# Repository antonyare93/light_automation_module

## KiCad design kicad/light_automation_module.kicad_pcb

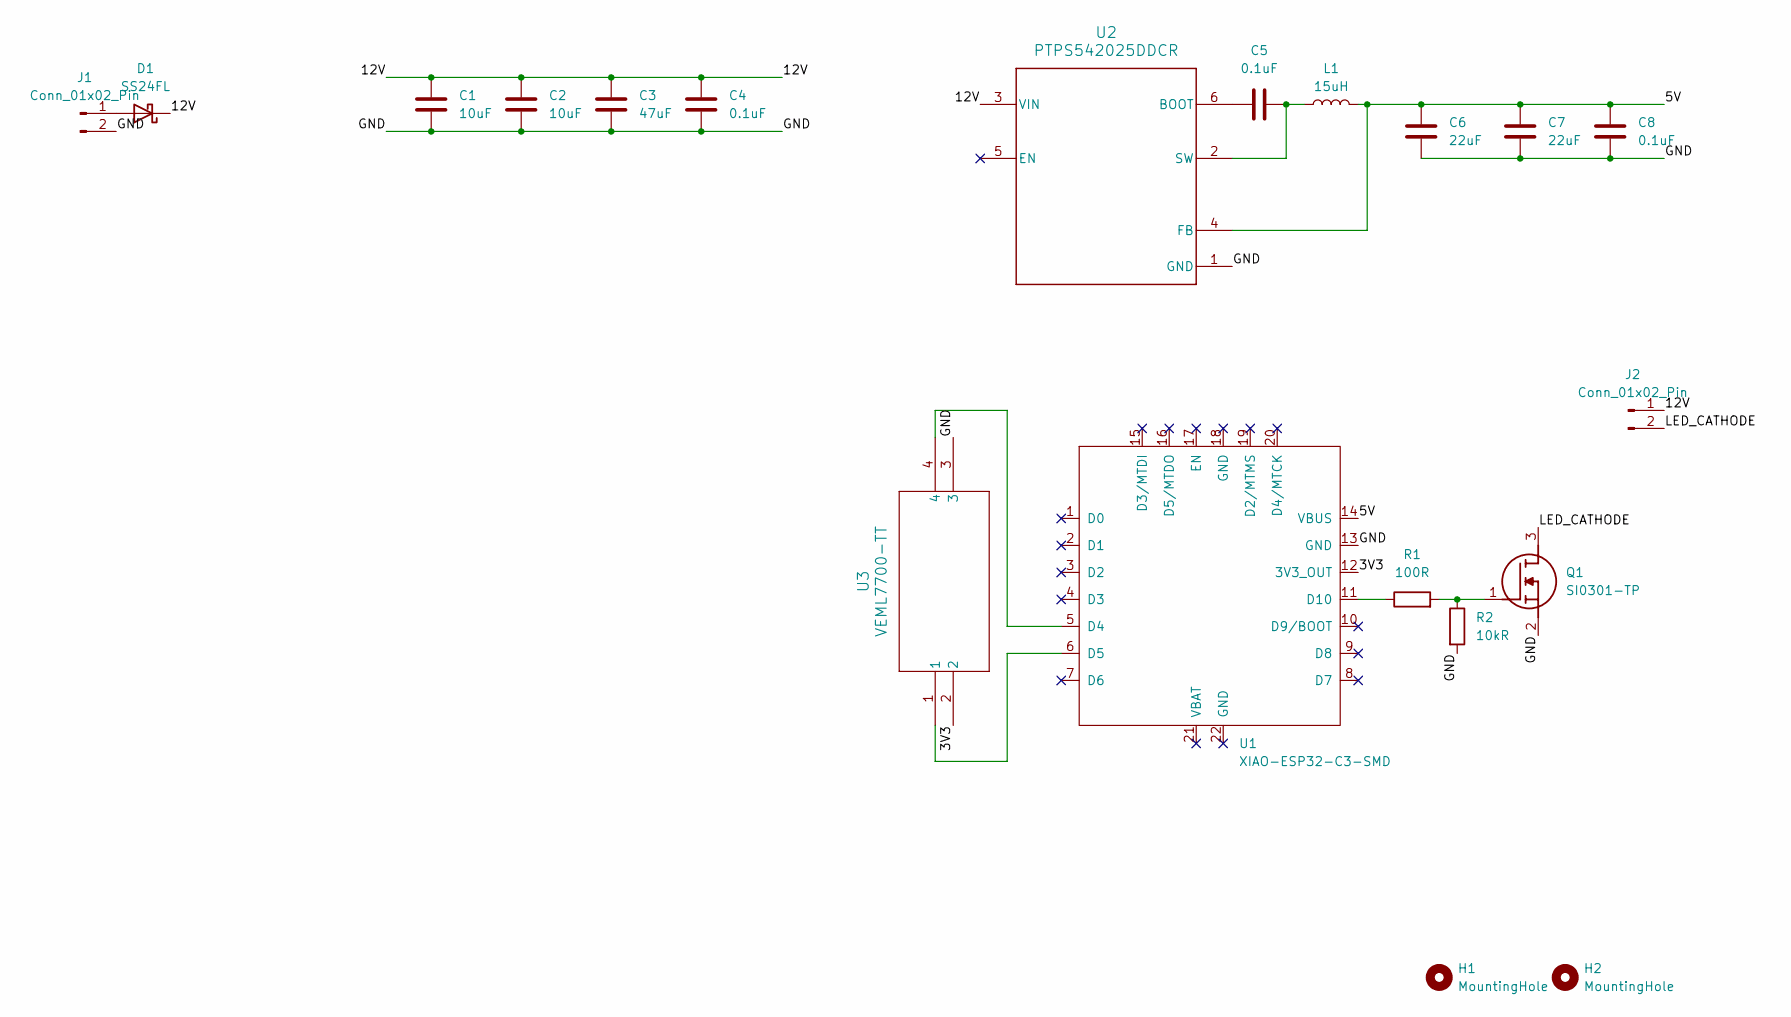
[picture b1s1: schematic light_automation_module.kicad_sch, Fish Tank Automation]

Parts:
C1, C2: 10uF; C_0603_1608Metric
C3: 47uF; CP_Radial_D6.3mm_P2.50mm
C4, C5, C8: 0.1uF; C_0603_1608Metric
C6, C7: 22uF; C_0603_1608Metric
D1: SS24FL; D_SOD-123F
H1, H2: MountingHole; MountingHole_3.2mm_M3
J1, J2: Conn_01x02_Pin; Pad 01x02
L1: 15uH; L_0603_1608Metric
Q1: SI0301-TP; SOT95P237X125-3N; Manufacturer_Part_Number SI0301-TP; Mouser Part Number 833-SI0301-TP
R1: 100R; R_0603_1608Metric
R2: 10kR; R_0603_1608Metric
U1: XIAO-ESP32-C3-SMD
U2: PTPS542025DDCR; DDC0006A-IPC_A
U3: VEML7700-TT; SMT_L7700-TT_VIS

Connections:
/3V3: U1.12 (3V3_OUT), U3.2
/5V: C6.1, C7.1, C8.1, L1.2, U1.14 (VBUS), U2.4 (FB)
/12V: C1.1, C2.1, C3.1, C4.1, D1.1 (K), J2.1, U2.3 (VIN)
/GND: C1.2, C2.2, C3.2, C4.2, C6.2, C7.2, C8.2, J1.2, Q1.2 (S), R2.2, U1.13 (GND), U2.1 (GND), U3.3
/LED_CATHODE: J2.2, Q1.3 (D)
unnamed: D1.2 (A), J1.1
unnamed: Q1.1 (G), R1.2, R2.1
unnamed: U1.5 (D4), U3.4
unnamed: U1.6 (D5), U3.1
unnamed: R1.1, U1.11 (D10)
unnamed: C5.2, U2.6 (BOOT)
unnamed: C5.1, L1.1, U2.2 (SW)

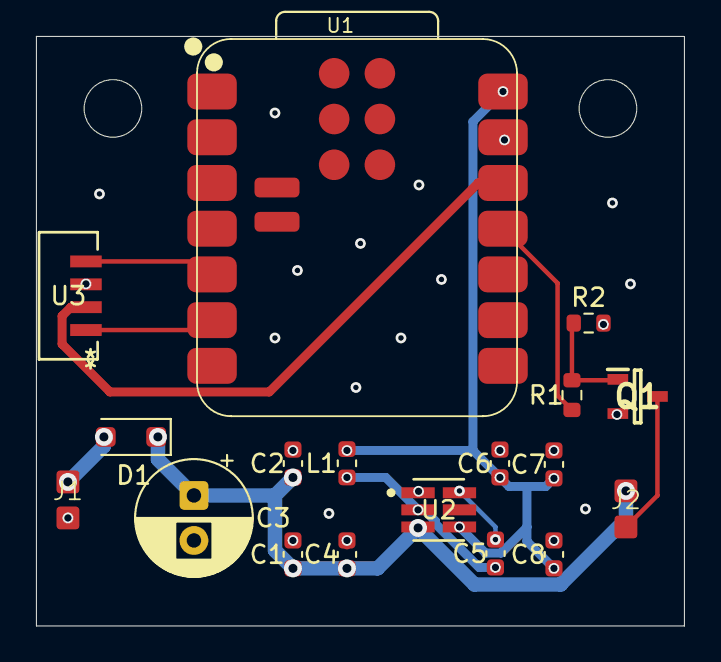
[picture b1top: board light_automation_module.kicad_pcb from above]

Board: 4 copper layers, 36.0 x 32.8 mm, 20 parts (0 on the bottom side), 12 nets.
